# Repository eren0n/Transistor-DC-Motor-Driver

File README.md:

# Transistor DC-Motor Driver
Custom DC Motor Driver With Arduino Nano and Transistors

# Read Before Use !!
Use "Enable" pins to control motor's rpm.</br>
If you send a "HIGH" signal to "Motor1.1" you have to send "LOW" signal to "Motor1.2". Or vice versa.</br>
If you send a "HIGH" signal to "Motor2.1" you have to send "LOW" signal to "Motor2.2". Or vice versa</br>
If you have "Clone Arduino" you have to use 9V batteries or less.</br>

# Arduino Pin Status
D13 : EMPTY</br>
D12 : MOTOR 2.2</br>
D11 : EMPTY</br>
D10 : EMPTY</br>
D9  : EMPTY</br>
D8  : EMPTY</br>
D7  : EMPTY</br>
D6  : ENABLE 2</br>
D5  : ENABLE 1</br>
D4  : MOTOR 2.1</br>
D3  : MOTOR 1.2</br>
D2  : MOTOR 1.1</br>
D1  : EMPTY</br>
D0  : EMPTY</br>
A0  : EMPTY</br>
A1  : EMPTY</br>
A2  : EMPTY</br>
A3  : EMPTY</br>
A4  : EMPTY</br>
A5  : EMPTY</br>
A6  : EMPTY</br>
A7  : EMPTY</br>
VIN : 9V</br>

# Explanation
This circuit is a school project of mine. This circuit isn't good and stable. It'd be better to use an integrated circuit like l239d instead of this circuit.</br>
If you want to use this card, please don't remove the disclaimer.

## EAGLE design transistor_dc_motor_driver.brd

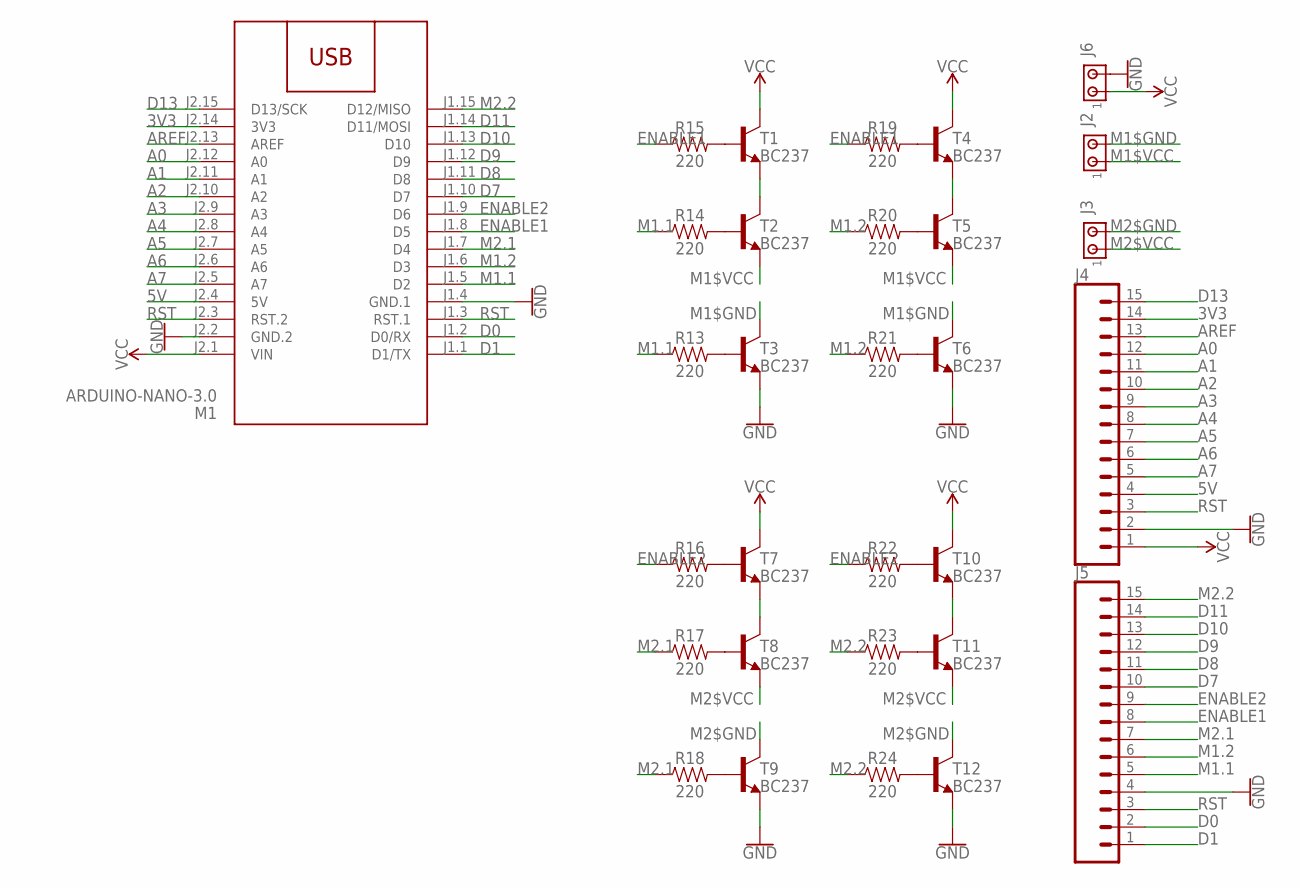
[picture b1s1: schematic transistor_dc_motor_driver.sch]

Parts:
J2, J3, J6: MTA02-156; 1X2MTA
J4, J5: CONN_15; 1X15
M1: ARDUINO-NANO-3.0
R13, R14, R15, R16, R17, R18, R19, R20, R21, R22, R23, R24: 220; AXIAL-0.3
T1, T2, T3, T4, T5, T6, T7, T8, T9, T10, T11, T12: BC237; TO92

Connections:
3V3: J4.14, M1.J2.14 (3V3)
5V: J4.4, M1.J2.4 (5V)
A0: J4.12, M1.J2.12 (A0)
A1: J4.11, M1.J2.11 (A1)
A2: J4.10, M1.J2.10 (A2)
A3: J4.9, M1.J2.9 (A3)
A4: J4.8, M1.J2.8 (A4)
A5: J4.7, M1.J2.7 (A5)
A6: J4.6, M1.J2.6 (A6)
A7: J4.5, M1.J2.5 (A7)
AREF: J4.13, M1.J2.13 (AREF)
D0: J5.2, M1.J1.2 (D0/RX)
D1: J5.1, M1.J1.1 (D1/TX)
D7: J5.10, M1.J1.10 (D7)
D8: J5.11, M1.J1.11 (D8)
D9: J5.12, M1.J1.12 (D9)
D10: J5.13, M1.J1.13 (D10)
D11: J5.14, M1.J1.14 (D11/MOSI)
D13: J4.15, M1.J2.15 (D13/SCK)
ENABLE1: J5.8, M1.J1.8 (D5), R15.P$1 (1), R19.P$1 (1)
ENABLE2: J5.9, M1.J1.9 (D6), R16.P$1 (1), R22.P$1 (1)
GND: J4.2, J5.4, J6.2, M1.J1.4 (GND.1), M1.J2.2 (GND.2), T3.1 (E), T6.1 (E), T9.1 (E), T12.1 (E)
M1$GND: J2.2, T3.3 (C), T6.3 (C)
M1$VCC: J2.1, T2.1 (E), T5.1 (E)
M1.1: J5.5, M1.J1.5 (D2), R13.P$1 (1), R14.P$1 (1)
M1.2: J5.6, M1.J1.6 (D3), R20.P$1 (1), R21.P$1 (1)
M2$GND: J3.2, T9.3 (C), T12.3 (C)
M2$VCC: J3.1, T8.1 (E), T11.1 (E)
M2.1: J5.7, M1.J1.7 (D4), R17.P$1 (1), R18.P$1 (1)
M2.2: J5.15, M1.J1.15 (D12/MISO), R23.P$1 (1), R24.P$1 (1)
unnamed: T1.1 (E), T2.3 (C)
unnamed: T7.1 (E), T8.3 (C)
unnamed: T10.1 (E), T11.3 (C)
unnamed: T4.1 (E), T5.3 (C)
unnamed: R13.P$2 (2), T3.2 (B)
unnamed: R14.P$2 (2), T2.2 (B)
unnamed: R15.P$2 (2), T1.2 (B)
unnamed: R16.P$2 (2), T7.2 (B)
unnamed: R17.P$2 (2), T8.2 (B)
unnamed: R18.P$2 (2), T9.2 (B)
unnamed: R19.P$2 (2), T4.2 (B)
unnamed: R20.P$2 (2), T5.2 (B)
unnamed: R21.P$2 (2), T6.2 (B)
unnamed: R22.P$2 (2), T10.2 (B)
unnamed: R23.P$2 (2), T11.2 (B)
unnamed: R24.P$2 (2), T12.2 (B)
RST: J4.3, J5.3, M1.J1.3 (RST.1), M1.J2.3 (RST.2)
VCC: J4.1, J6.1, M1.J2.1 (VIN), T1.3 (C), T4.3 (C), T7.3 (C), T10.3 (C)

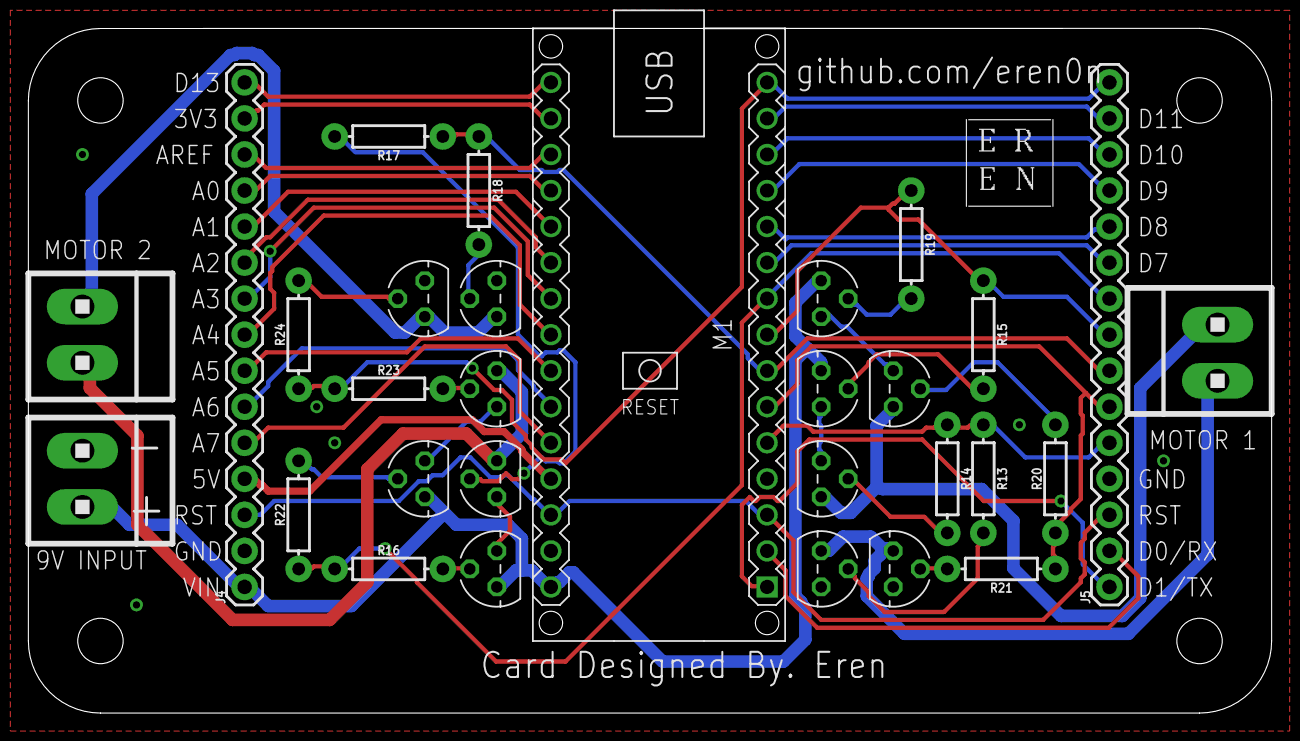
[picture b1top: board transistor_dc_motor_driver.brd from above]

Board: 2 copper layers, 87.6 x 48.3 mm, 30 parts (0 on the bottom side), 48 nets.

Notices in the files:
parts and their libraries:
SparkFun-Connectors: Licensing: Creative Commons ShareAlike 4.0 International - https://creativecommons.org/licenses/by-sa/4.0
diy-modules: Released under the Creative Commons Attribution 4.0 International License: http://creativecommons.org/licenses/by/4.0
